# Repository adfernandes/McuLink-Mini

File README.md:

# MCU-Link with KiCAD
This repository hosts different versions of the original NXP MCU-Link CMSIS-DAP debug probe as open source KiCAD versions. Both as standalone probe or integrated into your design.

Many thanks to *Dario Scheuber* and his work to make this project possible!

## Background
This is the work of Dario Scheuber who created this debug probe as student at the Lucerne University of Applied Sciences and Arts at [IET](https://www.hslu.ch/en/lucerne-school-of-engineering-architecture/about-us/organization/institute/engineering-and-technology/elektrotechnik/). The project was done under the guidance of Prof. Erich Styger.

See blog article on https://mcuoneclipse.com/2024/02/06/versatile-oshw-mini-mcu-link-debug-probe-external-on-board-or-embedded/ for additional details.

## Features
This is an open hardware version of the NXP MCU-Link CMSIS-DAP debug probe, with following features and differences to the original MCU-Link:
- Open hardware design with KiCad
- Firmware compatibility with MCU-Link (LinkServer, CMSIS-DAP, ARM DAPLink)
- Dual-Layer design for lower costs
- USB-C connector instead of  Micro-USB
- USB-C connector usable to debug the LPC55S69
- 30% smaller than the original MCU-Link
- Firmware/boot push button instead of jumper
- Micro connector for UART connection instead of pin header
- Supports only 3.3V targets (no level shifters)
- Standalone version as external debug probe
- On-Board version: Solder external debug probe on your custom board (castellated pins)
- Embedded version: copy-paste into your custom board KiCad design
- BOM with assembly costs: ~$12/piece for 100 units

## Folders
- enclosure: 3D printed enclosure
- hardware: KiCad and hardware related files

## Links
- Article: https://mcuoneclipse.com/2024/02/06/versatile-oshw-mini-mcu-link-debug-probe-external-on-board-or-embedded/
- NXP MCU-Link: https://www.nxp.com/design/design-center/software/development-software/mcuxpresso-software-and-tools-/mcu-link-debug-probe:MCU-LINK
- KiCad: https://www.kicad.org/

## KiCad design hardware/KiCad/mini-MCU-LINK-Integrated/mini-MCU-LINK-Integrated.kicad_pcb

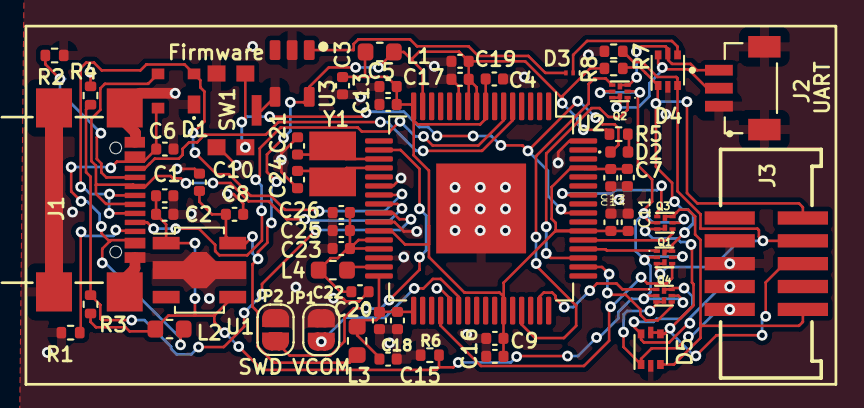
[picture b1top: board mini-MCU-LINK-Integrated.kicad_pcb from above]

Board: 2 copper layers, 57 parts (0 on the bottom side), 39 nets.

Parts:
C1, C10: 10u; C_0402_1005Metric
C2, C4, C5, C7, C8, C9, C11, C17, C18, C25: 100n; C_0402_1005Metric
C3: 4u7; C_0402_1005Metric
C6, C12, C13, C14, C16: 10n; C_0402_1005Metric
C15, C22, C26: 22u; C_0402_1005Metric
C19, C20, C23: 47p; C_0402_1005Metric
C21, C24: 8p; C_0402_1005Metric
D1: PRTR5V0U2X; SOT143B
D2: LED_RED; LED_0402_1005Metric
D3: PMEG3005AESFYL; Nexperia_DSN0603-2_0.6x0.3mm_P0.4mm
D4, D5: PESD5V0L5UV; SOT-666
J1: USB4110-GF-A_REVB; USB_C_Receptacle_GCT_USB4110-GF-A
J2: BM03B-SRSS-TB; JST_BM03B-SRSS-TB_LF__SN_
J3: Conn_02x05_Odd_Even; SWD_Pin_Header_Straight_2x05_Pitch1.27mm_SMD
JP1: VCOM disable; SolderJumper-2_P1.3mm_Open_RoundedPad1.0x1.5mm
JP2: SWD disable; SolderJumper-2_P1.3mm_Open_RoundedPad1.0x1.5mm
L1, L2, L3: MI0603J601R-10; L_0603_1608Metric
L4: 4u7; L_0603_1608Metric
Q1, Q2, Q3, Q4: PMDXB290UNE; SOT1216
R1, R2: 5k1; R_0402_1005Metric
R3, R6: 10k; R_0402_1005Metric
R4: 20k; R_0402_1005Metric
R5: 2k; R_0402_1005Metric
R7, R8: 100k; R_0402_1005Metric
SW1: KMR221GLFS; SW_C_K_KMR2
U1: XC6227C331PR-G; SOT-89-5
U2: LPC55S69JBD64; LQFP-64-1EP_10x10mm_P0.5mm_EP5x5mm
U3: STMPS2141STR; SOT95P280X145-5N
Y1: 16.000MHz; CX3225GA16000D0PTVCC

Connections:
+3V3: C8.1, C10.1, C17.1, C19.1, L1.1, L3.1, R5.1, R8.1, U1.5 (VOUT), U2.9 (VDDA), U2.10 (VREFP), U2.15 (PIO0_31), U3.5 (IN)
+5V: C1.1, C2.1, L2.2, Q1.2 (G), Q1.5 (G), Q2.2 (G), Q2.5 (G), Q3.2 (G), Q3.5 (G), Q4.2 (G), Q4.5 (G), R3.2, R6.1, U1.1 (CE), U1.4 (VIN)
/mini MCU-LINK Debug and UART interface/DETECT: Q4.4 (S), U2.50 (PIO0_22)
/mini MCU-LINK Debug and UART interface/ISP_CTRL: Q4.1 (S), U2.47 (PIO0_14)
/mini MCU-LINK Debug and UART interface/PIO0_5-ISP_EN-LED1_CTRL: D2.1 (K), SW1.1, SW1.3, U2.56 (PIO0_5)
/mini MCU-LINK Debug and UART interface/RESET: Q3.1 (S), U2.58 (PIO0_19)
/mini MCU-LINK Debug and UART interface/RXD: Q2.4 (S), U2.45 (PIO0_24)
/mini MCU-LINK Debug and UART interface/SWCLK: Q1.4 (S), U2.36 (PIO0_0)
/mini MCU-LINK Debug and UART interface/SWDIO: Q1.1 (S), U2.52 (PIO0_2)
/mini MCU-LINK Debug and UART interface/SWD_DISABLE: JP2.1 (A), U2.18 (PIO0_27)
/mini MCU-LINK Debug and UART interface/SWO: Q3.4 (S), U2.53 (PIO0_3)
/mini MCU-LINK Debug and UART interface/TARGET_DETECT: D5.1 (K1), J3.9, Q4.3 (D)
/mini MCU-LINK Debug and UART interface/TARGET_ISP_CTRL: D5.6 (K5), J3.7, Q4.6 (D)
/mini MCU-LINK Debug and UART interface/TARGET_RESET: D5.3 (K2), J3.10, Q3.6 (D)
/mini MCU-LINK Debug and UART interface/TARGET_RXD: D4.5 (K4), J2.1, Q2.3 (D)
/mini MCU-LINK Debug and UART interface/TARGET_SWCLK: D4.3 (K2), J3.4, Q1.3 (D), R7.1
/mini MCU-LINK Debug and UART interface/TARGET_SWDIO: D4.1 (K1), J3.2, Q1.6 (D), R8.2
/mini MCU-LINK Debug and UART interface/TARGET_SWO: D5.4 (K3), D5.5 (K4), J3.6, Q3.3 (D)
/mini MCU-LINK Debug and UART interface/TARGET_TXD: D4.6 (K5), J2.2, Q2.6 (D)
/mini MCU-LINK Debug and UART interface/TXD: Q2.1 (S), U2.51 (PIO0_25)
/mini MCU-LINK Debug and UART interface/VCC: D3.1 (K), D4.4 (K3)
/mini MCU-LINK Debug and UART interface/VCOM_DISABLE: JP1.1 (A), U2.38 (PIO0_18)
/mini MCU-LINK Power and USB/MCU_VDDIO: C3.1, C4.1, C5.1, C7.1, C9.1, C11.1, C12.1, C13.1, C14.1, C16.1, L1.2, U2.8 (VDD), U2.16 (VDD), U2.27 (USB1_3V3), U2.43 (VDD), U2.54 (VDD), U2.61 (USB0_3V3)
/mini MCU-LINK Power and USB/Q+: C24.1, U2.20 (XTAL32M_P), Y1.2
/mini MCU-LINK Power and USB/Q-: C21.1, U2.19 (XTAL32M_N), Y1.1
/mini MCU-LINK Power and USB/USB_D+: D1.2 (I/O1), J1.A6 (D+), J1.B6 (D+), U2.23 (USB1_DP)
/mini MCU-LINK Power and USB/USB_D-: D1.3 (I/O2), J1.A7 (D-), J1.B7 (D-), U2.24 (USB1_DM)
/mini MCU-LINK Power and USB/USB_VBUS: C6.1, D1.4 (VCC), J1.A4/B9 (VBUS), J1.B4/A9 (VBUS), L2.1
GND: C1.2, C2.2, C3.2, C4.2, C5.2, C6.2, C7.2, C8.2, C9.2, C10.2, C11.2, C12.2, C13.2, C14.2, C15.2, C16.2, C17.2, C18.2, C19.2, C20.2, C21.2, C22.2, C23.2, C24.2, C25.2, C26.2, D1.1 (GND), D4.2 (A), D5.2 (A), J1.A1/B12 (GND), J1.B1/A12 (GND), J1.S1 (SHIELD), J2.3, J2.S1 (SHIELD), J2.S2 (SHIELD__1), J3.3, J3.5, JP1.2 (B), JP2.2 (B), R1.1, R2.1, R4.1, R6.2, R7.2, SW1.2, SW1.4, SW1.5 (SHIELD), U1.2 (VSS), U2.11 (VSSA), U2.22 (USB1_VSS), U2.26 (USB1_VSS), U2.30 (VSS_DCDC), U2.37 (PIO0_9), U2.64 (USB0_VSS), U2.65 (EP), U3.2 (GND), U3.4 (EN)
unnamed: D2.2 (A), R5.2
unnamed: D3.2 (A), U3.1 (OUT)
unnamed: J1.A5 (CC1), R2.2
unnamed: J1.B5 (CC2), R1.2
unnamed: C22.1, C23.1, C25.1, C26.1, L4.2, U2.28 (VDD_PMU), U2.29 (FB)
unnamed: L4.1, U2.31 (LX)
unnamed: C15.1, C18.1, C20.1, L3.2, U2.32 (VBAT_DCDC), U2.33 (VBAT_PMU)
unnamed: R3.1, R4.2, U2.25 (USB1_VBUS)
PROBE_SWDCLK: J1.A8 (SBUS1), U2.6 (PIO0_11)
PROBE_SWDIO: J1.B8 (SBUS2), U2.5 (PIO0_12)

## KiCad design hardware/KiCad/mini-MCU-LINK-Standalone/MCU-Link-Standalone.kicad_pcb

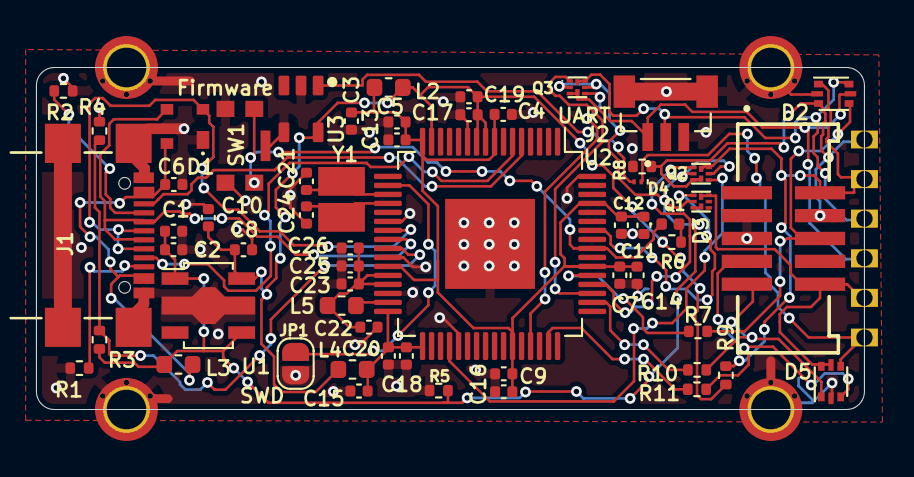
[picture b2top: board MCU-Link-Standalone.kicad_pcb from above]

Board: 2 copper layers, 46.0 x 19.0 mm, 69 parts (1 on the bottom side), 38 nets.

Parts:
C1, C10: 10u; C_0402_1005Metric
C2, C4, C5, C7, C8, C9, C11, C17, C18, C25: 100n; C_0402_1005Metric
C3: 4u7; C_0402_1005Metric
C6, C12, C13, C14, C16: 10n; C_0402_1005Metric
C15, C22, C26: 22u; C_0402_1005Metric
C19, C20, C23: 47p; C_0402_1005Metric
C21, C24: 8p; C_0402_1005Metric
D1: PRTR5V0U2X; SOT143B
D2, D5: PESD5V0L5UV; SOT-666
D3: LED_RED; LED_0402_1005Metric
D4: PMEG3005AESFYL; Nexperia_DSN0603-2_0.6x0.3mm_P0.4mm
H1, H2, H3, H4: MountingHole_Pad; MountingHole_2.2mm_M2_ISO7380_Pad_TopBottom_with_holes
H5: RXD; castellated pin
H6: SWCLK; castellated pin
H7: TXD; castellated pin
H8: SWDIO; castellated pin
H9: 3.3V; castellated pin
H10: Reset; castellated pin
J1: USB4110-GF-A_REVB; USB_C_Receptacle_GCT_USB4110-GF-A
J2: BM03B-SRSS-TB; JST_BM03B-SRSS-TB_LF__SN_
J3: Conn_02x05_Odd_Even; SWD_Pin_Header_Straight_2x05_Pitch1.27mm_SMD
JP1: SWD disable; SolderJumper-2_P1.3mm_Open_RoundedPad1.0x1.5mm
L1: Logo HSLU; Hochschule_Luzern_New
L2, L3, L4: MI0603J601R-10; L_0603_1608Metric
L5: 4u7; L_0603_1608Metric
Q1, Q2, Q3: PMDXB290UNE; SOT1216
R1, R2: 5k1; R_0402_1005Metric
R3, R5: 10k; R_0402_1005Metric
R4: 20k; R_0402_1005Metric
R6, R10: 2k; R_0402_1005Metric
R7: 100; R_0402_1005Metric
R8, R9: 100k; R_0402_1005Metric
R11: 10; R_0402_1005Metric
SW1: KMR221GLFS; SW_C_K_KMR2
U1: XC6227C331PR-G; SOT-89-5
U2: LPC55S69JBD64; LQFP-64-1EP_10x10mm_P0.5mm_EP5x5mm
U3: STMPS2141STR; SOT95P280X145-5N
Y1: 16.000MHz; CX3225GA16000D0PTVCC

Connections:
+3V3: C8.1, C10.1, C17.1, C19.1, L2.1, L4.1, R6.1, R9.1, U1.5 (VOUT), U2.9 (VDDA), U2.10 (VREFP), U2.15 (PIO0_31), U3.5 (IN)
+5V: C1.1, C2.1, L3.2, Q1.2 (G), Q2.2 (G), Q2.5 (G), Q3.2 (G), Q3.5 (G), R3.2, R5.1, U1.1 (CE), U1.4 (VIN)
/Debug and UART Interface/PIO0_5-ISP_EN-LED1_CTRL: D3.1 (K), SW1.1, SW1.3, U2.56 (PIO0_5)
/Debug and UART Interface/RESET: Q1.1 (S), U2.58 (PIO0_19)
/Debug and UART Interface/RXD: Q3.4 (S), U2.45 (PIO0_24)
/Debug and UART Interface/SWCLK: Q2.4 (S), U2.36 (PIO0_0)
/Debug and UART Interface/SWDIO: Q2.1 (S), U2.52 (PIO0_2)
/Debug and UART Interface/TARGET_DETECT: R10.1, U2.50 (PIO0_22)
/Debug and UART Interface/TARGET_ISP_CTRL: R11.1, U2.47 (PIO0_14)
/Debug and UART Interface/TARGET_RESET: D5.5 (K4), D5.6 (K5), H10.1, J3.10, Q1.6 (D)
/Debug and UART Interface/TARGET_RXD: D2.5 (K4), H5.1, J2.1, Q3.3 (D)
/Debug and UART Interface/TARGET_SWCLK: D2.3 (K2), J3.4, Q2.3 (D), R8.1
/Debug and UART Interface/TARGET_SWDIO: D2.1 (K1), H8.1, J3.2, Q2.6 (D), R9.2
/Debug and UART Interface/TARGET_SWO: R7.2, U2.53 (PIO0_3)
/Debug and UART Interface/TARGET_TXD: D2.6 (K5), H7.1, J2.2, Q3.6 (D)
/Debug and UART Interface/TXD: Q3.1 (S), U2.51 (PIO0_25)
/Debug and UART Interface/VCC: D4.1 (K), D5.4 (K3), H9.1
/MCU-LINK Power and USB/MCU_VDDIO: C3.1, C4.1, C5.1, C7.1, C9.1, C11.1, C12.1, C13.1, C14.1, C16.1, L2.2, U2.8 (VDD), U2.16 (VDD), U2.27 (USB1_3V3), U2.43 (VDD), U2.54 (VDD), U2.61 (USB0_3V3)
/MCU-LINK Power and USB/Q+: C24.1, U2.20 (XTAL32M_P), Y1.2
/MCU-LINK Power and USB/Q-: C21.1, U2.19 (XTAL32M_N), Y1.1
/MCU-LINK Power and USB/USB_D+: D1.2 (I/O1), J1.A6 (D+), J1.B6 (D+), U2.23 (USB1_DP)
/MCU-LINK Power and USB/USB_D-: D1.3 (I/O2), J1.A7 (D-), J1.B7 (D-), U2.24 (USB1_DM)
/MCU-LINK Power and USB/USB_VBUS: C6.1, D1.4 (VCC), J1.A4/B9 (VBUS), J1.B4/A9 (VBUS), L3.1
GND: C1.2, C2.2, C3.2, C4.2, C5.2, C6.2, C7.2, C8.2, C9.2, C10.2, C11.2, C12.2, C13.2, C14.2, C15.2, C16.2, C17.2, C18.2, C19.2, C20.2, C21.2, C22.2, C23.2, C24.2, C25.2, C26.2, D1.1 (GND), D2.2 (A), D5.2 (A), H1.1, H2.1, H3.1, H4.1, J1.A1/B12 (GND), J1.B1/A12 (GND), J1.S1 (SHIELD), J2.3, J2.S1 (SHIELD), J2.S2 (SHIELD__1), J3.3, J3.5, JP1.2 (B), R1.1, R2.1, R4.1, R5.2, R8.2, SW1.2, SW1.4, SW1.5 (SHIELD), U1.2 (VSS), U2.11 (VSSA), U2.22 (USB1_VSS), U2.26 (USB1_VSS), U2.30 (VSS_DCDC), U2.37 (PIO0_9), U2.64 (USB0_VSS), U2.65 (EP), U3.2 (GND), U3.4 (EN)
unnamed: D2.4 (K3), J3.6, R7.1
unnamed: D3.2 (A), R6.2
unnamed: D4.2 (A), U3.1 (OUT)
unnamed: D5.1 (K1), J3.9, R10.2
unnamed: D5.3 (K2), J3.7, R11.2
unnamed: J1.A5 (CC1), R2.2
unnamed: J1.B5 (CC2), R1.2
unnamed: JP1.1 (A), U2.18 (PIO0_27)
unnamed: C22.1, C23.1, C25.1, C26.1, L5.2, U2.28 (VDD_PMU), U2.29 (FB)
unnamed: L5.1, U2.31 (LX)
unnamed: C15.1, C18.1, C20.1, L4.2, U2.32 (VBAT_DCDC), U2.33 (VBAT_PMU)
unnamed: R3.1, R4.2, U2.25 (USB1_VBUS)
PROBE_SWDCLK: J1.A8 (SBUS1), U2.6 (PIO0_11)
PROBE_SWDIO: J1.B8 (SBUS2), U2.5 (PIO0_12)

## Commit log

2025-04-19 Remove extraneous PMEG3005AESFYL whitespace/newline
2025-05-29 added schematic files
2025-10-29 Cleanup, MR version is hosted in different repository here: https://github.com/ErichStyger/MCU-Link-MR
